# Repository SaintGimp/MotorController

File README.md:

# MotorController

The board files use the libraries and design rules from https://github.com/SaintGimp/Eagle.

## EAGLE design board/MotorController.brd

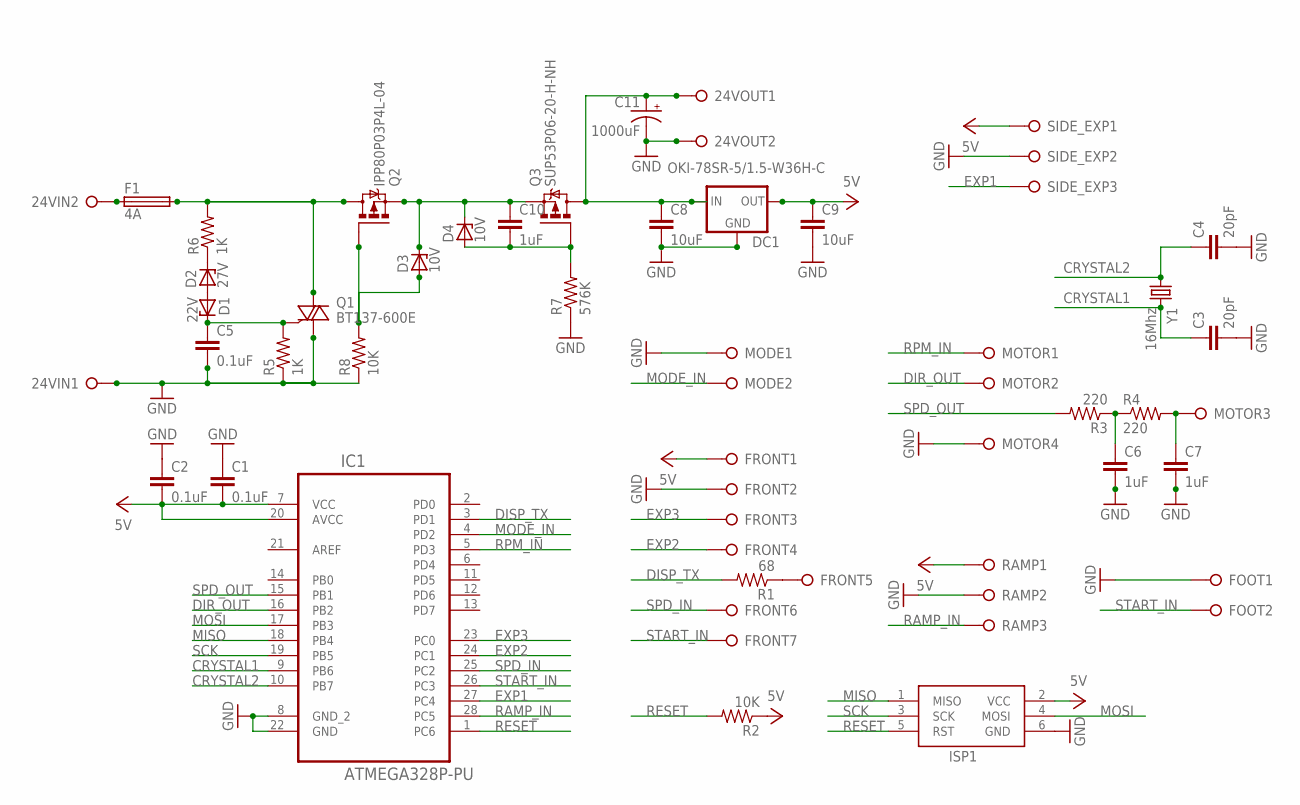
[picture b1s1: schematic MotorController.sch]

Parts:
24VIN, 24VOUT: PINHD-1X2BIG; 1X02-BIG
C1, C2, C5: 0.1uF; CAPACITOR-2.5MM
C3, C4: 20pF; CAPACITOR-2.5MM
C6, C7, C10: 1uF; CAPACITOR-2.5MM
C8, C9: 10uF; CAPACITOR-5MM
C11: 1000uF; CAP-POL-25-14
D1: 22V; ZDIO-7.5
D2: 27V; ZDIO-7.5
D3, D4: 10V; ZDIO-7.5
DC1: OKI-78SR-5/1.5-W36H-C; DC-CONV
F1: 4A; FUSE_HOLDER_5X20MM
FOOT: PINHD-1X2BIG; 1X02-BIG
FRONT: PINHD-1X7BIG; 1X07-BIG
IC1: ATMEGA328P-PU; DIP28
ISP1: ICSP-HEADER-6; ICSP-HEADER
MODE: PINHD-1X2BIG; 1X02-BIG
MOTOR: PINHD-1X4BIG; 1X04-BIG
Q1: BT137-600E; TO220BH-NO-HOLE
Q2: IPP80P03P4L-04; TO220BH-NO-HOLE
Q3: SUP53P06-20-H-NH; TO220BH-NO-HOLE
R1: 68; AXIAL-7.5MM
R2, R8: 10K; AXIAL-7.5MM
R3, R4: 220; AXIAL-7.5MM
R5, R6: 1K; AXIAL-7.5MM
R7: 576K; AXIAL-7.5MM
RAMP: PINHD-1X3BIG; 1X03-BIG
SIDE_EXP: PINHD-1X3BIG; 1X03-BIG
Y1: 16Mhz; CRYSTAL-V

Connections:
24V: F1.2, Q1.P2 (A2), Q2.P2 (D), R6.P$2 (2)
24V-PROTECTED: 24VOUT.1, C8.1, C11.+, DC1.P1 (IN), Q3.P2 (D)
CRYSTAL1: C3.1, IC1.9 (PB6), Y1.2
CRYSTAL2: C4.1, IC1.10 (PB7), Y1.1
DIR_OUT: IC1.16 (PB2), MOTOR.2
DISP_TX: IC1.3 (PD1), R1.P$2 (2)
EXP1: IC1.27 (PC4), SIDE_EXP.3
EXP2: FRONT.4, IC1.24 (PC1)
EXP3: FRONT.3, IC1.23 (PC0)
GND: 24VIN.1, 24VOUT.2, C1.1, C2.1, C3.2, C4.2, C5.2, C6.2, C7.2, C8.2, C9.2, C11.-, DC1.P2 (GND), FOOT.1, FRONT.2, IC1.8 (GND_2), IC1.22 (GND), ISP1.6 (GND), MODE.1, MOTOR.4, Q1.P1 (A1), R5.P$1 (1), R7.P$1 (1), R8.P$1 (1), RAMP.2, SIDE_EXP.2
MISO: IC1.18 (PB4), ISP1.1 (MISO)
MODE_IN: IC1.4 (PD2), MODE.2
MOSI: IC1.17 (PB3), ISP1.4 (MOSI)
unnamed: C6.1, R3.P$1 (1), R4.P$1 (1)
unnamed: 24VIN.2, F1.1
unnamed: D3.A, Q2.P1 (G), R8.P$2 (2)
unnamed: D2.C, R6.P$1 (1)
unnamed: D1.A, D2.A
unnamed: C5.1, D1.C, Q1.P3 (G), R5.P$2 (2)
unnamed: FRONT.5, R1.P$1 (1)
unnamed: C10.1, D3.C, D4.C, Q2.P3 (S), Q3.P3 (S)
unnamed: C7.1, MOTOR.3, R4.P$2 (2)
unnamed: C10.2, D4.A, Q3.P1 (G), R7.P$2 (2)
RAMP_IN: IC1.28 (PC5), RAMP.3
RESET: IC1.1 (PC6), ISP1.5 (RST), R2.P$2 (2)
RPM_IN: IC1.5 (PD3), MOTOR.1
SCK: IC1.19 (PB5), ISP1.3 (SCK)
SPD_IN: FRONT.6, IC1.25 (PC2)
SPD_OUT: IC1.15 (PB1), R3.P$2 (2)
START_IN: FOOT.2, FRONT.7, IC1.26 (PC3)
VCC: C1.2, C2.2, C9.1, DC1.P3 (OUT), FRONT.1, IC1.7 (VCC), IC1.20 (AVCC), ISP1.2 (VCC), R2.P$1 (1), RAMP.1, SIDE_EXP.1

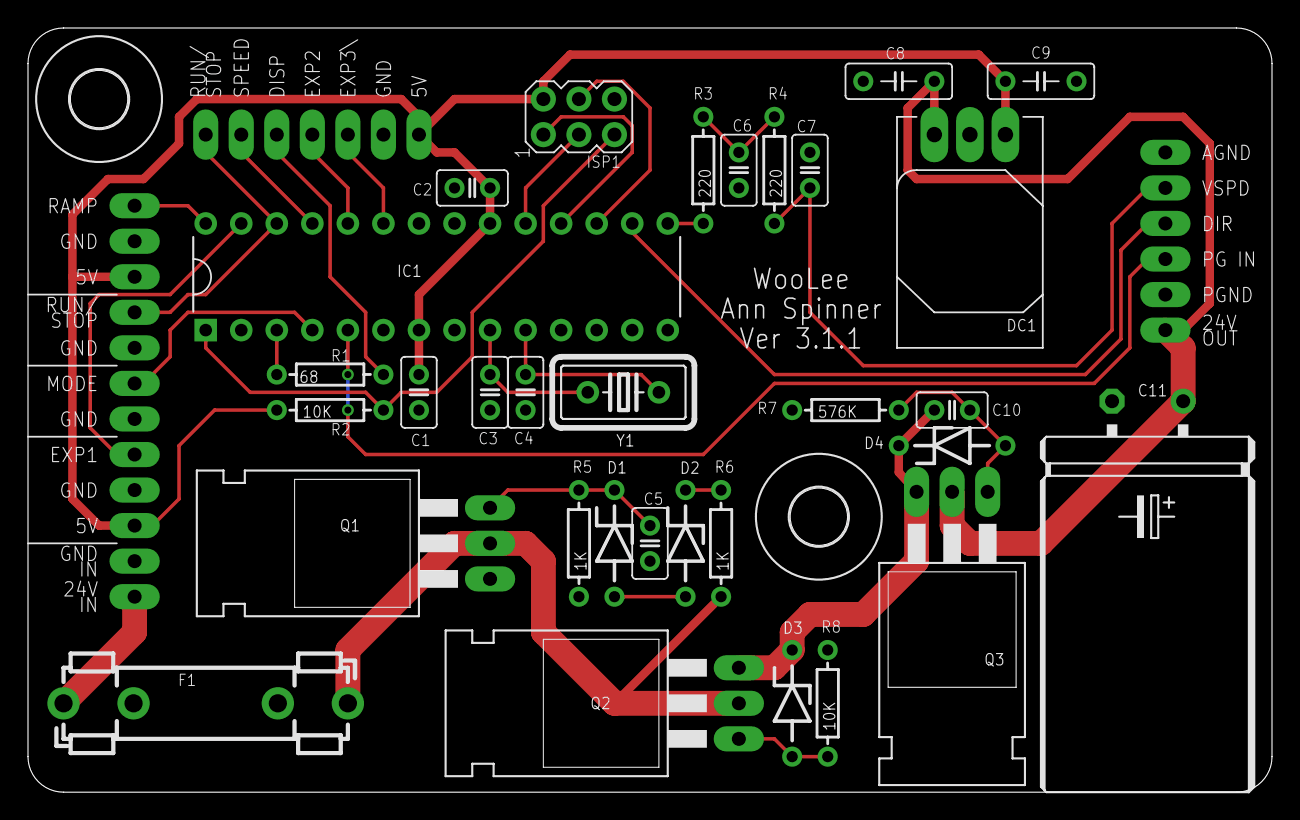
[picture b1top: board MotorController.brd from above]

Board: 2 copper layers, 88.9 x 54.6 mm, 41 parts (0 on the bottom side), 31 nets.

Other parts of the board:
U$2, U$4: 4,1

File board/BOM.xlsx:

Qty | Value | Device | Package | Parts | Manufacturer Part Number | Description | Notes
1 | 1000uF | CAP-POL-25-14 | CAP-POL-25-14 | C11 | EEU-FR1H102 | Polarized Capacitor | Expensive but long-life, 470uF version is EEU-FR1H471B
2 | 10uF | CAPACITOR-5MM | CAPACITOR-5MM | C8, C9 | FK20X7S1H106K | Ceramic Capacitor | Ammo pack
3 | 1uF | CAPACITOR-2.5MM | CAPACITOR-2.5MM | C6, C7, C10 | FK14X7R1H105K | Ceramic Capacitor | Bulk (maybe)
3 | 0.1uF | CAPACITOR-2.5MM | CAPACITOR-2.5MM | C1, C2, C5 | K104K15X7RF53L2 | Ceramic Capacitor | Bulk
2 | 20pF | CAPACITOR-2.5MM | CAPACITOR-2.5MM | C3, C4 | SR151A200JAR | Ceramic Capacitor | Bulk
1 | 576K | RESISTOR-7.5MM | AXIAL-7.5MM | R7 | MFR-25FBF52-576K |  | Bulk
2 | 10K | RESISTOR-7.5MM | AXIAL-7.5MM | R2, R8 | MFR-25FBF52-10K |  | Bulk
2 | 1K | RESISTOR-7.5MM | AXIAL-7.5MM | R5, R6 | MFR-25FBF52-1K |  | Bulk
2 | 220 | RESISTOR-7.5MM | AXIAL-7.5MM | R3, R4 | MF1/4DC2200F |  | Bulk
1 | 68 | RESISTOR-7.5MM | AXIAL-7.5MM | R1 | MF1/4DC68R0F |  | Bulk
1 | 27V | ZENER-7.5 | ZDIO-7.5 | D2 | 1N5254B-TAP | Zener Diode | Ammo pack
1 | 22V | ZENER-7.5 | ZDIO-7.5 | D1 | 1N5251B-TAP | Zener Diode | Ammo pack
2 | 10V | ZENER-7.5 | ZDIO-7.5 | D3, D4 | 1N5240B-TAP | Zener Diode | Ammo pack
1 | BT139X-600E | TRIAC-H | TO220BH | Q1 | BT137-600E,127 | TRIAC
2 | SUP53P06-20-E3 | SUP53P06-20-E3 | TO220BH | Q2, Q3 | SUP53P06-20-E3 | P-Channel MOSFET
1 | OKI-78SR-5/1.5-W36H-C | DC-CONV | DC-CONV | DC1 | OKI-78SR-5/1.5-W36H-C | DC-DC Converter
1 | ATMEGA328P-PU | ATMEGA328P-PU | DIP28 | IC1 | ATMEGA328P-PU | 8-bit Microcontroller with In-System Programmable Flash
1 | 28P | Socket | DIP28 | IC1 | 1-2199298-9 |  | Optional
1 | 16Mhz | CRYSTAL-V | CRYSTAL-V | Y1 | ATS16A | Crystal Oscillator
1 | 4A-MEDIUM-BLOW | FUSE | FUSE_5X20MM | F1 | 5MT 4-R |  | Derated 25% per standard, consider fast-blow?
2 | 4A | FUSE CLIP | FUSE_CLIP_5MM | F1 | 01000056Z
4 | SWITCH-MOMENTARY-6MM | SWITCH-MOMENTARY-6MM | TACTILE-SWITCH-6MM | S1, S2, S3, S4 | B3F-1020
 | version 3.1.1

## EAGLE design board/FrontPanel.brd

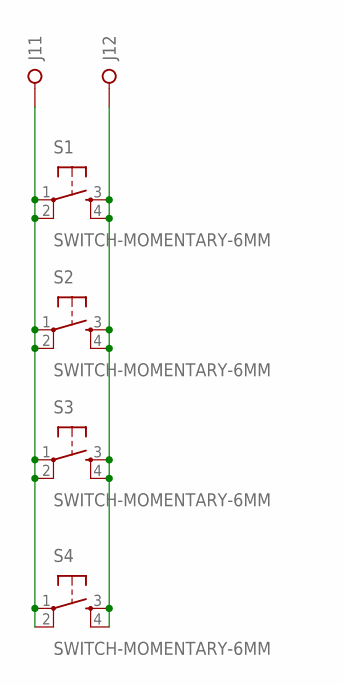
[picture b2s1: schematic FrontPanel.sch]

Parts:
J1: PINHD-1X2BIG; 1X02-BIG
S1, S2, S3, S4: SWITCH-MOMENTARY-6MM; TACTILE-SWITCH-6MM

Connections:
unnamed: J1.1, S1.1, S1.2, S2.1, S2.2, S3.1, S3.2, S4.1, S4.2
unnamed: J1.2, S1.3, S1.4, S2.3, S2.4, S3.3, S3.4, S4.3, S4.4

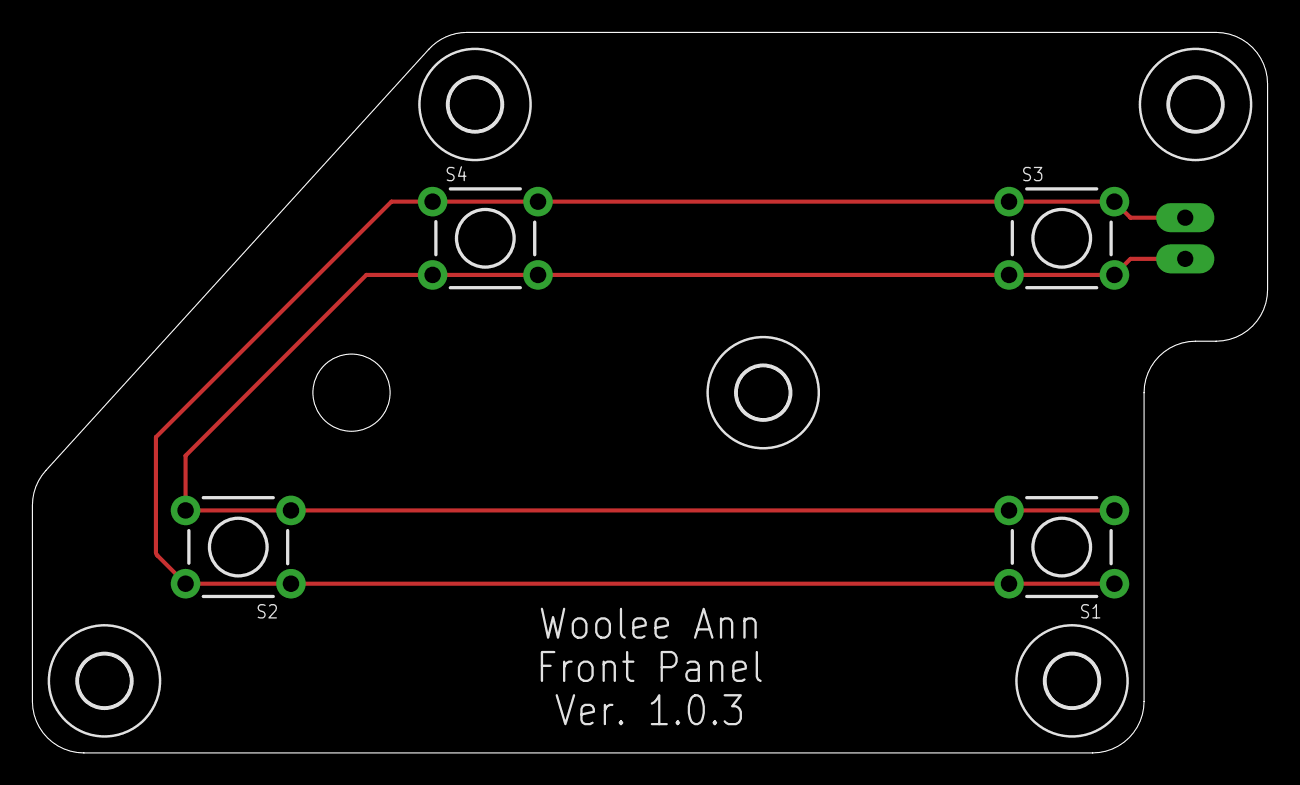
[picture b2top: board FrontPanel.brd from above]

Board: 2 copper layers, 76.2 x 44.5 mm, 10 parts (0 on the bottom side), 2 nets.

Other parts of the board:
U$1, U$2, U$3, U$4, U$5: 3,2

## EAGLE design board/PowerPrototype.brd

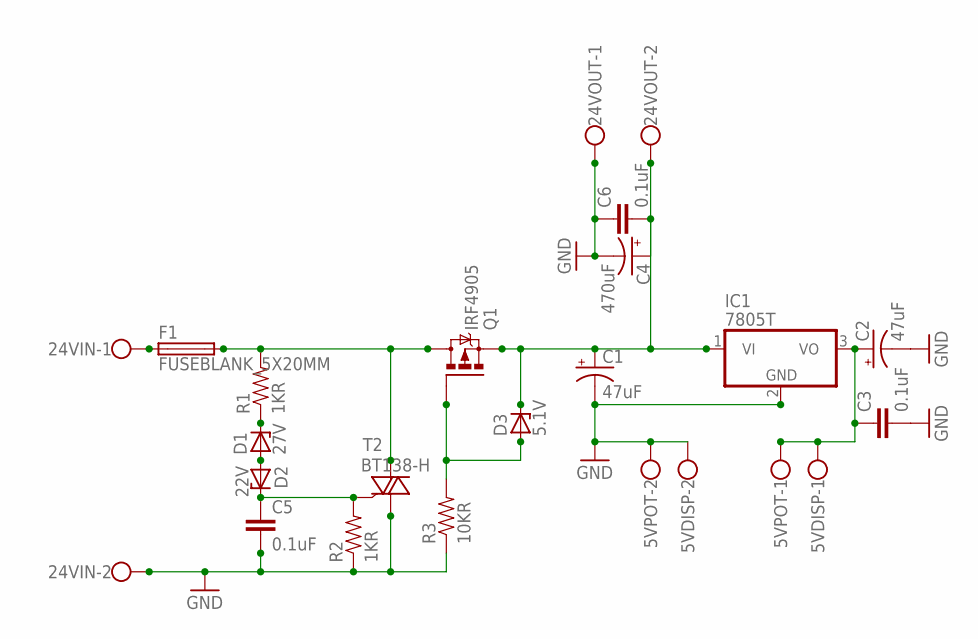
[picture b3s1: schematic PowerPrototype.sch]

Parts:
5VDISP, 5VPOT, 24VIN, 24VOUT: W237-102
C1, C2: 47uF; E2,5-5
C3, C5, C6: 0.1uF; CAP-PTH-5MM
C4: 470uF; E2,5-5
D1: 27V; ZDIO-5
D2: 22V; ZDIO-5
D3: 5.1V; ZDIO-7.5
F1: FUSEBLANK_5X20MM; FUSE_HOLDER_5X20MM
IC1: 7805T; TO220H
Q1: IRF4905; TO220BH
R1, R2: 1KR; AXIAL-0.3
R3: 10KR; AXIAL-0.3
T2: BT138-H; TO220BH

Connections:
GND: 5VDISP.2, 5VPOT.2, 24VIN.2, 24VOUT.1, C1.-, C2.-, C3.2, C4.-, C5.2, C6.1, IC1.2 (GND), R2.P$1 (1), R3.P$1 (1), T2.T1 (A1)
unnamed: 24VOUT.2, C1.+, C4.+, C6.2, D3.C, IC1.1 (VI), Q1.S
unnamed: F1.2, Q1.D, R1.P$2 (2), T2.T2 (A2)
unnamed: 24VIN.1, F1.1
unnamed: D3.A, Q1.G, R3.P$2 (2)
unnamed: D1.C, R1.P$1 (1)
unnamed: D1.A, D2.A
unnamed: C5.1, D2.C, R2.P$2 (2), T2.G
unnamed: 5VDISP.1, 5VPOT.1, C2.+, C3.1, IC1.3 (VO)

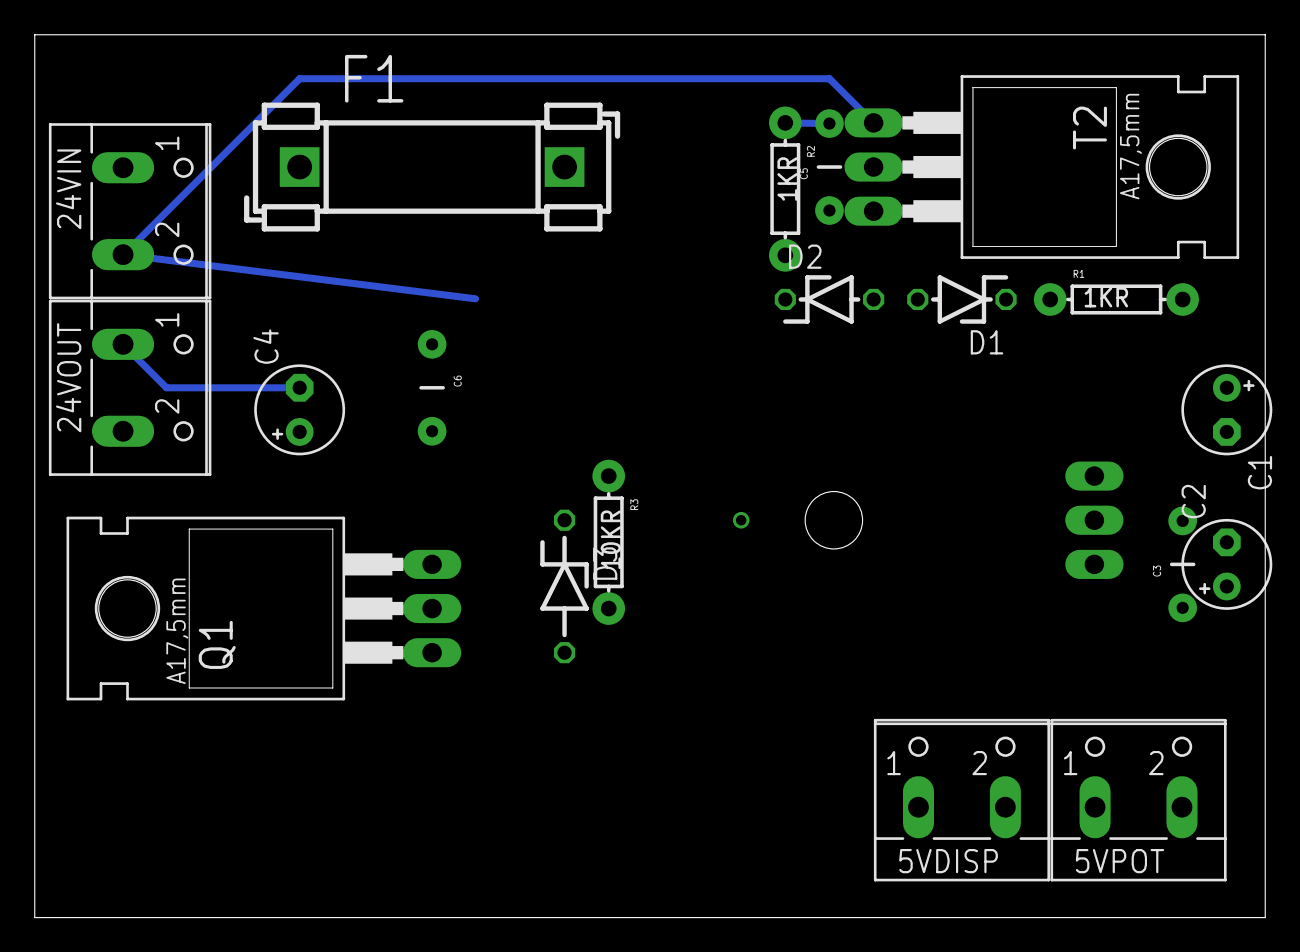
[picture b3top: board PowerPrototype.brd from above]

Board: 2 copper layers, 70.8 x 50.8 mm, 20 parts (1 on the bottom side), 9 nets.

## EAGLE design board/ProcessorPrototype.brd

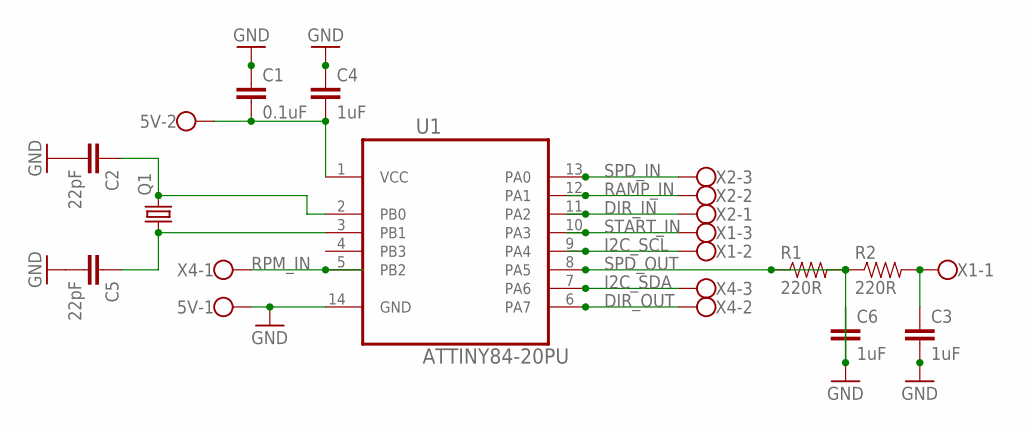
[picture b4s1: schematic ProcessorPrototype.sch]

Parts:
5V: W237-102
C1: 0.1uF; CAP-PTH-5MM
C2, C5: 22pF; CAP-PTH-5MM
C3, C4, C6: 1uF; CAP-PTH-5MM
Q1: CRYSTALHC18U-V; HC18U-V
R1, R2: 220R; AXIAL-0.3
U1: ATTINY84-20PU; DIP254P762X533-14
X1, X2, X4: W237-103

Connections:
DIR_IN: U1.11 (PA2), X2.1
DIR_OUT: U1.6 (PA7), X4.2
GND: 5V.1, C1.1, C2.2, C3.2, C4.1, C5.2, C6.1, U1.14 (GND)
I2C_SCL: U1.9 (PA4), X1.2
I2C_SDA: U1.7 (PA6), X4.3
unnamed: C6.2, R1.P$1 (1), R2.P$1 (1)
unnamed: C3.1, R2.P$2 (2), X1.1
unnamed: 5V.2, C1.2, C4.2, U1.1 (VCC)
unnamed: C5.1, Q1.1, U1.3 (PB1)
unnamed: C2.1, Q1.2, U1.2 (PB0)
RAMP_IN: U1.12 (PA1), X2.2
RPM_IN: U1.5 (PB2), X4.1
SPD_IN: U1.13 (PA0), X2.3
SPD_OUT: R1.P$2 (2), U1.8 (PA5)
START_IN: U1.10 (PA3), X1.3

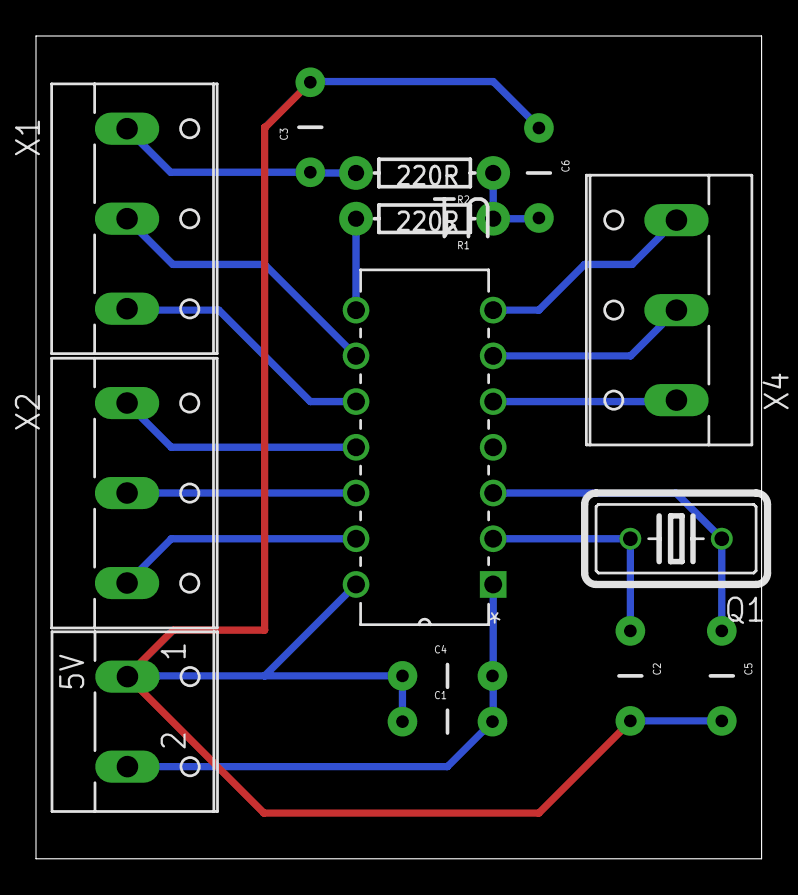
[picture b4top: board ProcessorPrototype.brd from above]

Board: 2 copper layers, 40.3 x 45.7 mm, 14 parts (0 on the bottom side), 15 nets.

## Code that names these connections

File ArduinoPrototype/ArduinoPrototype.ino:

#include <Bounce.h>

const int CLOCKWISE = 1;
const int COUNTER_CLOCKWISE = 0;

#if defined(__AVR_ATmega328P__)

// Arduino Pins
const int speedInPin = A0;
const int rateOfSpeedChangeInPin = A1;
const int speedOutPin = 9;
const int onOffSwitchInPin = 7;
const int directionSwitchInPin = 6;
const int directionOutputPin = 5;

#elif defined( __AVR_ATtinyX4__ )

// ATMEL ATTINY84 / arduino-tiny mapping
//
//                           +-\/-+
//                     VCC  1|    |14  GND
//             (D  0)  PB0  2|    |13  AREF (D 10) (A 0)
//             (D  1)  PB1  3|    |12  PA1  (D  9) (A 1)
//       RESET         PB3  4|    |11  PA2  (D  8) (A 2)
//  PWM  INT0  (D  2)  PB2  5|    |10  PA3  (D  7) (A 3)
//  PWM  (A 7) (D  3)  PA7  6|    |9   PA4  (D  6) (A 4)
//  PWM  (A 6) (D  4)  PA6  7|    |8   PA5  (D  5) (A 5)   PWM
//                           +----+
//
const int speedInPin = A0;
const int rateOfSpeedChangeInPin = A1;
const int speedOutPin = 5;
const int onOffSwitchInPin = 7;
const int directionSwitchInPin = 8;
const int directionOutputPin = 6;

#elif defined( __AVR_ATtinyX5__ )

// ATMEL ATTINY85 / arduino-tiny mapping
//                           +-\/-+
//  Ain0       (D  5)  PB5  1|    |8   VCC
//  Ain3       (D  3)  PB3  2|    |7   PB2  (D  2)  INT0  Ain1
//  Ain2       (D  4)  PB4  3|    |6   PB1  (D  1)        pwm1
//                     GND  4|    |5   PB0  (D  0)        pwm0
//                           +----+
//
// NOTE!!!! This requires use of the RESET pin so either RSTDISBL fuse must be set
// which prevents normal reprogramming or the rateOfChange pot has to be used as a
// rheostat and as R1 of a voltage divider so that the voltage on A0 never goes
// below ~1.5V and resets the MCU.
//
const int speedInPin = A3;
const int rateOfSpeedChangeInPin = A0;
const int speedOutPin = 0;
const int onOffSwitchInPin = 2;
const int directionSwitchInPin = 1;
const int directionOutputPin = 4;

#endif

// Settings and limits
const int switchDebounceTime = 30;
const int minimumDelay = 5;
const int maximumDelay = 40;
const int minimumSpeed = 10;
// 10K ohm potentiometers probably won't get all the way to 1024
// and we want to make sure that max feasible input = max motor speed
const int potentiometerCeiling = 1000;

// Switches using the Bounce library for debouncing
Bounce onOffSwitch = Bounce(onOffSwitchInPin, switchDebounceTime);
Bounce directionSwitch = Bounce(directionSwitchInPin, switchDebounceTime);

// State variables
int targetSpeed = 0;
int currentSpeed = 0;
int delayBetweenAdjustments = 15;
boolean powerEnabled = false;
int targetDirection = CLOCKWISE;
int currentDirection = CLOCKWISE;

void setup()
{
  pinMode(onOffSwitchInPin, INPUT_PULLUP);
  pinMode(directionSwitchInPin, INPUT_PULLUP);
  pinMode(directionOutputPin, OUTPUT);
  // We don't have to set pin mode for analog inputs
  
  // TODO: check startup logic to make sure this is right
  digitalWrite(directionOutputPin, targetDirection);
}

void loop()
{
  onOffSwitch.update();
  if (onOffSwitch.fallingEdge())
  {
    powerEnabled = !powerEnabled;
  }
  
  if (powerEnabled)
  {
    targetSpeed = ReadPotentiometer(speedInPin);
    targetSpeed = map(targetSpeed, 0, potentiometerCeiling, minimumSpeed, 255);
  
    delayBetweenAdjustments = ReadPotentiometer(rateOfSpeedChangeInPin);
    delayBetweenAdjustments = map(delayBetweenAdjustments, 0, potentiometerCeiling, minimumDelay, maximumDelay);
  }
  else
  {
    targetSpeed = 0;
  }

  directionSwitch.update();
  targetDirection = directionSwitch.read();

  if (targetDirection == CLOCKWISE)
  {
    targetSpeed = abs(targetSpeed);
  }
  else
  {
    targetSpeed = -abs(targetSpeed);
  }
  
  if (currentSpeed == 0 && currentDirection != targetDirection)
  {
    // We're at zero speed and want to switch directions.
    // The motor spec sheet says we have to wait .5 seconds before
    // switching to make sure that the motor has come to a full stop.

    // TODO: do we need to hit the run/stop control line in order to
    // guarentee that the motor is stopped?
    
    delay(500);
    digitalWrite(directionOutputPin, targetDirection);
    currentDirection = targetDirection;
  }
  
  currentSpeed += SlewToward(currentSpeed, targetSpeed);
  analogWrite(speedOutPin, abs(currentSpeed));           
  
  // Rather than trying to write a fixed-delay loop we're being lazy and using a
  // variable-deplay loop to control the rate at which we change the motor speed.
  // This should be fine because we don't have anything urgent that we need to do
  // in between adjustments anyway and the input response lag even at maximum delay
  // will never be noticable to the user.
  delay(delayBetweenAdjustments);                     
}

int ReadPotentiometer(int pin)
{
  int value = analogRead(pin);
  value = constrain(value, 0, potentiometerCeiling);
  
  return value;
}

int SlewToward(int currentValue, int targetValue)
{
  if (currentValue > targetValue)
  {
    return -1;
  }
  else if (currentValue < targetValue)
  {
    return 1;
  }
  else
  {
    return 0;
  }
}

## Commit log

2013-12-04 One pot controlling speed output
2013-12-05 Added rate pot, on/off and direction switches
2013-12-07 Support ATTiny84 and ATTiny85 MCUs
2013-12-07 Arduino-tiny core for ATTiny MCUs
2013-12-07 Tweaks
2013-12-07 Assume that ATTiny85 is going to need RESET disabled
2013-12-10 Fixed PWM output and renamed sketch
2013-12-10 Tweaked speed minimum and ramp min/max to match specs
2013-12-14 Include Eagle design files and move stuff around
2013-12-14 Add a ground pour on the bottom plane and route all power and signal traces on the top
2013-12-14 Tweaked schematic
2013-12-14 Switch to a top GND pour
2013-12-14 Switch to a horizontal regulator and change board layout to fit
2013-12-14 License file
2013-12-28 Board tweaks, prototype labels
2013-12-28 Only allow power on if current speed is 0
2014-01-02 Parameter tweaks based on prototype trials
2014-01-02 Add RPM display and move to ATTiny84
2014-01-03 Change RPM calculation to expect one pulse every 90 deg of rotation
2014-04-13 V2 prototype
2014-04-17 Initial pass at a PCB and added clock code
2014-04-28 PCB improvements
2015-04-08 Update with current design rules and current library
2015-04-08 Pull up reset line
2015-04-09 Replace I2C with serial library
2015-04-11 Refit LCDi2cNHD library for serial
2015-04-11 Stop at zero speed when changing direction rather than starting up again
2015-05-26 New board layout
2015-05-26 Restore resistor values
2015-05-26 Add dimensions
2015-05-28 Board tweaks
2015-05-28 Board layout improvements
2015-05-28 Fix position of D3 label
2015-05-29 Remove old libraries and design files
2015-05-29 Remove old prototype files
2015-05-29 Add readme
2015-06-06 Change triac value
2015-06-06 Updated BOM
2015-07-10 Fix power input labels and increase isolation for ground plane
2015-07-10 Oversample the speed pot. Even better would be to have true hysteresis.
2015-07-10 More BOM updates
2015-07-13 Start front panel board
2015-07-13 Switch to pin headers and ATMega328P
2015-07-13 Double the maximum delay for ramp
2015-07-18 Version 3, many changes
2015-07-18 Add soft-start capability to avoid high inrush current
2015-07-25 Remove unneeded file
2015-07-25 Front panel design with dimension markings
2015-07-25 Many changes for version 3
2015-07-25 Clean up front panel
2015-07-25 Front panel tweaks
2015-07-27 Miter corners of control board
2015-07-27 Adjust front panel layout
2015-07-27 Spread out front panel buttons, flip terminal silkscreen to back
2015-07-29 Improve bypass cap layout
2015-07-29 Adjust spacing of DAC filter and ICSP header
2015-07-29 Adjust clearance of MCU power trace
2015-07-29 Revert MCU power trace
2015-07-29 Tweak label
2015-08-08 Tweak TO220 packages and add board heatsink
2015-08-08 Fix the label order of caps
2015-08-08 More adjustments to BOM and parts labels
2015-08-15 Even more BOM and label adjustments
2015-08-16 Update firmware to ATMega328P and add stop damping
2015-08-16 Revert back to previous triac circuit
2015-08-16 Connect RPM IN to pin 5 which supports interrupts
2015-08-16 Bump board version
2015-08-28 Tweak mask settings in design rules
2015-08-28 Bump patch version
2015-10-27 Update DRU for front panel and bump version
2015-10-27 Update library and DRU for main board
2015-10-28 Switched to 60V MOSFETs and updated BOM and inventory
2015-11-14 Add installation files for Windows and delete unused libraries
2015-11-15 Add pause at the end of install script and add test procedures doc
2016-07-06 Add the ability to reset the clock by shorting EXP3 and toggle debug display by shorting EXP2
2016-07-06 Add hole to front panel
2016-07-06 Update inventory
2016-07-06 Firmware version 3.1.0
2016-08-11 Switch to the Bounce2 library
2016-08-11 Remove delay from main loop and control motor updates with a specific delay
2016-08-11 Convert periodic tasks to use ArduinoThread library
2016-08-14 Add libraries as direct project files so we always have the correct versions
2016-08-15 Shrink the loop time by not multisampling the ramp pot, which doesn't need it
2016-08-15 Firmware version 3.1.1
2016-09-12 Updated inventory
2016-10-06 Debug firmware to troubleshoot clock problems
2016-10-06 Fix clock bug on debug branch
2016-10-06 Fix an off-by-one bug in the way we load clock values
2016-10-06 Firmware 3.1.2
2016-10-06 Final fix on debug branch
2017-09-15 Update stock
2019-05-02 Fix a missing line in board outline and generate JCLPCB gerbers
2019-05-02 Updated test procedures
2019-05-02 Updated stock levels
2020-01-09 Initial commit of V2 code
2020-01-09 vNext redesign WIP
2022-05-07 Update BOM and test procedures
2022-05-11 Test doc updates
2022-09-20 Fix overflow bug in hours display
2022-09-20 Add new 3.1.3 firmware and update script files
2023-08-21 Changes to support RioRand motor driver module
2023-08-21 Firmware 4.0.0 and updated install scripts

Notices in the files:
parts and their libraries:
SparkFun-Capacitors: Licensing: CC v3.0 Share-Alike You are welcome to use this library for commercial purposes.
